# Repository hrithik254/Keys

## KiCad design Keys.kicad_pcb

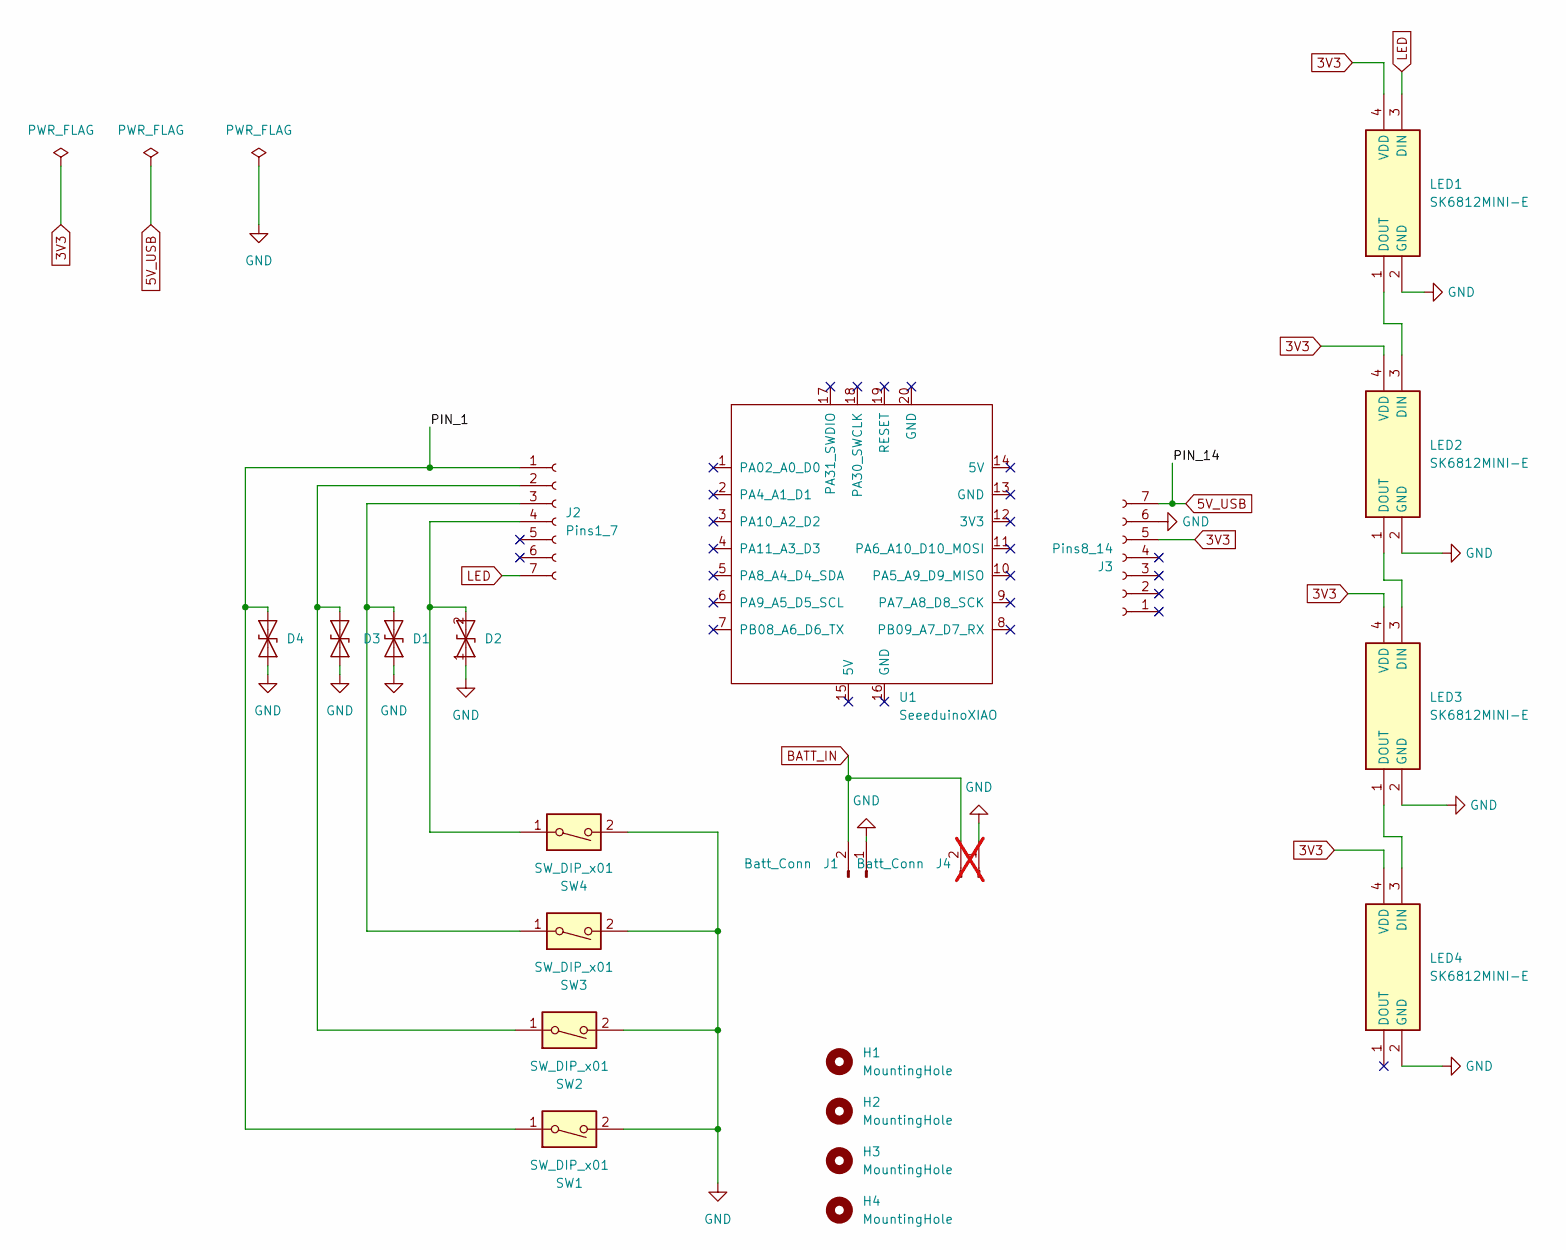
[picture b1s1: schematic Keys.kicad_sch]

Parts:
D1, D2, D3, D4: ESD9B3.3ST5G; D_0603_1608Metric_Pad1.05x0.95mm_HandSolder
H1, H2, H3, H4: MountingHole; MountingHole_2.2mm_M2_DIN965_Pad
J1: Batt_Conn; JST_PH_S2B-PH-K_1x02_P2.00mm_Horizontal
J2: Pins1_7; PinSocket_1x07_P2.54mm_Vertical
J3: Pins8_14; PinSocket_1x07_P2.54mm_Vertical
J4: Batt_Conn; C_1210_3225Metric; not fitted
LED1, LED2, LED3, LED4: SK6812MINI-E; SK6812_mini; Manufacturer_Part_Number SK6812MINI-E
SW1, SW2, SW3, SW4: SW_DIP_x01; Kailh_socket_MX
U1: SeeeduinoXIAO; Seeeduino XIAO-MOUDLE14P-2.54-21X17.8MM

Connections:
3V3: J3.5, LED1.4 (VDD), LED2.4 (VDD), LED3.4 (VDD), LED4.4 (VDD)
5V_USB: J3.7
/PIN_1: D4.2 (A2), J2.1, SW1.1
BATT_IN: J1.2, J4.2
GND: D1.1 (A1), D2.1 (A1), D3.1 (A1), D4.1 (A1), J1.1, J3.6, J4.1, LED1.2 (GND), LED2.2 (GND), LED3.2 (GND), LED4.2 (GND), SW1.2, SW2.2, SW3.2, SW4.2
LED: J2.7, LED1.3 (DIN)
unnamed: D1.2 (A2), J2.3, SW3.1
unnamed: D2.2 (A2), J2.4, SW4.1
unnamed: D3.2 (A2), J2.2, SW2.1
unnamed: LED1.1 (DOUT), LED2.3 (DIN)
unnamed: LED2.1 (DOUT), LED3.3 (DIN)
unnamed: LED3.1 (DOUT), LED4.3 (DIN)

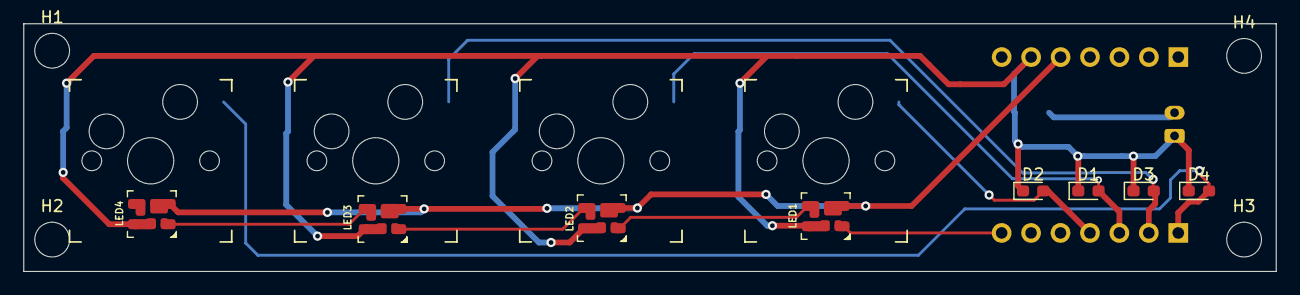
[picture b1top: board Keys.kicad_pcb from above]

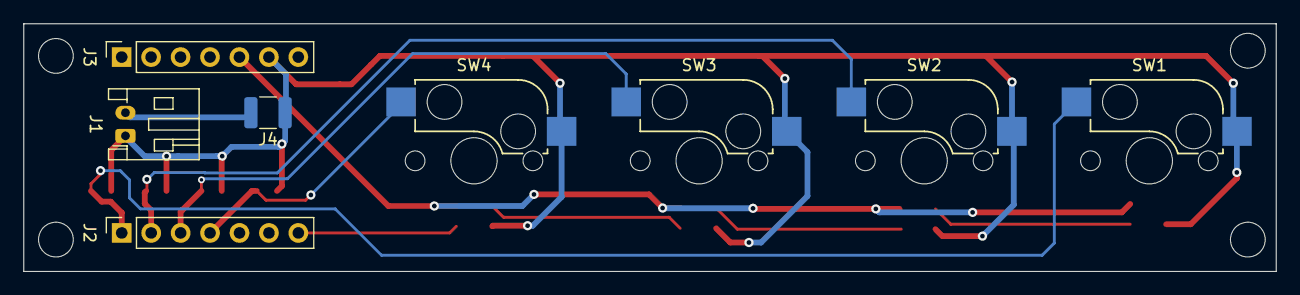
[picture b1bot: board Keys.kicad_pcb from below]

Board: 2 copper layers, 108.1 x 21.4 mm, 20 parts (4 on the bottom side), 11 nets.

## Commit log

2023-07-02 pcb layout
    verified schematic now moving on to routing
2023-07-15 no changes
